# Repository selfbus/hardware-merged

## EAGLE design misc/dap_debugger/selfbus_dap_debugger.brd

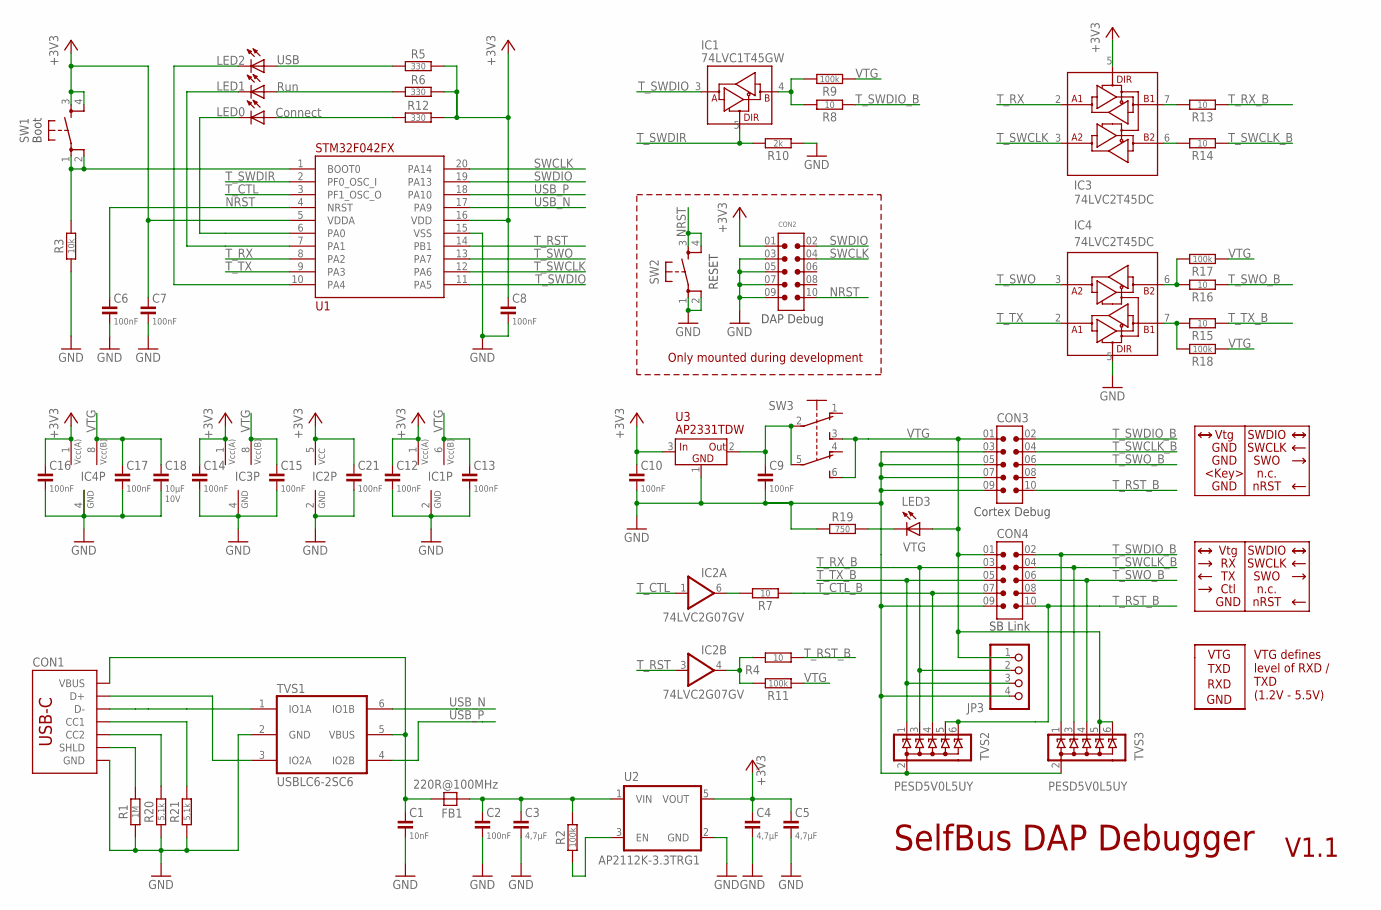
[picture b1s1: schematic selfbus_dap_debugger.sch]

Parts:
C1: 10nF; C0805
C2, C6, C7, C8, C9, C10, C12, C13, C14, C15, C16, C17, C21: 100nF; C0805
C3, C4, C5: 4,7µF; C0805
C18: 10µF; C0805; VOLTAGE 10V
CON1: XKB U262-161N-4BVC11; USB-C-16P-2LAYER-PADS
CON2, CON3: SHF-105-01-X-D-TH; SAMTEC_SHF-105-01-X-D-TH
CON4: SAMTEC-LTMM-105-02-T-D
FB1: 220R@100MHz; FB0805; MOUSER# 810-MPZ2012S221ATD25; LCSC#2 C139188
IC1: 74LVC1T45GW; SOT363; MOUSER# 771-74LVC1T45GW125; LCSC# C478004
IC2: 74LVC2G07GV; SOT23-6; MOUSER# 771-LVC2G07GV125; LCSC# C548568
IC3: 74LVC2T45DC; VSSOP8(0.5); MOUSER# 595-SN74LVC2T45DCUT; LCSC# C15741
IC4: 74LVC2T45DC; VSSOP8(0.5)
JP3: PINHD-1X4; 1X04
LED0: Connect; LED_3MM_GREEN
LED1: Run; LED_3MM_YELLOW
LED2: USB; LED_3MM_GREEN
LED3: VTG; LED_3MM_RED
R1: 1M; R0805
R2, R9, R11, R17, R18: 100k; R0805
R3: 10k; R0805
R4, R7, R8, R13, R14, R15, R16: 10; R0805
R5, R6, R12: 330; R0805
R10: 2k; R0805
R19: 750; R0805
R20, R21: 5,1k; R0805
SW1: BOOT; TACT_SWITCH_6X6_SNAP-IN_17; MOUSER# 688-SKHHDHA010; LCSC# C139811
SW2: RESET; TACT_SWITCH_6X6_SNAP-IN_17; MOUSER# 688-SKHHDHA010; LCSC# C139811
SW3: XKB7070-Z; XKB7070
TVS1: USBLC6-2SC6; SOT-23-6L; MOUSER# 511-USBLC6-2SC6; LCSC#2 C2687116
TVS2: PESD5V0L5UY; SOT363; MOUSER# 771-PESD5V0L5UY-T/R; LCSC# C179747
TVS3: PESD5V0L5UY; SOT363
U1: STM32F042FX; TSSOP20; MOUSER# 511-STM32F042F4P6; LCSC# C81002
U2: AP2112K-3.3TRG1; SOT23-5; MOUSER# 621-AP2112K-3.3TRG1; LCSC# C51118
U3: AP2331TDW; SC59; MOUSER# 621-AP2331W-7; LCSC# C460346

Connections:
+3V3: C4.1, C5.1, C7.1, C8.1, C10.1, C12.1, C14.1, C16.1, C21.1, CON2.01 (1), IC1.1 (VCC(A)), IC2.5 (VCC), IC3.1 (VCC(A)), IC3.5 (DIR), IC4.1 (VCC(A)), R5.2, R6.2, R12.2, SW1.3, SW1.4, U1.5 (VDDA), U1.16 (VDD), U2.5 (VOUT), U3.3 (IN)
D_N: CON1.A7 (D-), CON1.B7 (D-), TVS1.1 (IO1A)
D_P: CON1.A6 (D+), CON1.B6 (D+), TVS1.3 (IO2A)
GND: C1.2, C2.2, C3.2, C4.2, C5.2, C6.2, C7.2, C8.2, C9.2, C10.2, C12.2, C13.2, C14.2, C15.2, C16.2, C17.2, C18.2, C21.2, CON1.GND, CON1.GND2 (GND), CON2.03 (3), CON2.05 (5), CON2.07 (7), CON2.09 (9), CON3.03 (3), CON3.05 (5), CON3.07 (7), CON3.09 (9), CON4.09 (9), IC1.2 (GND), IC2.2 (GND), IC3.4 (GND), IC4.4 (GND), IC4.5 (DIR), JP3.4, R1.1, R3.1, R10.1, R19.1, R20.1, R21.1, SW2.1, SW2.2, TVS1.2 (GND), TVS2.2 (A), TVS3.2 (A), U1.15 (VSS), U2.2 (GND), U3.1 (GND)
LED0: LED0.C, U1.6 (PA0)
LED1: LED1.C, U1.7 (PA1)
unnamed: CON1.SHLD1 (SHLD), CON1.SHLD2 (SHLD), CON1.SHLD3 (SHLD), CON1.SHLD4 (SHLD), R1.2
unnamed: CON1.B5 (CC2), R20.2
unnamed: CON1.A5 (CC1), R21.2
unnamed: R2.1, U2.3 (EN)
unnamed: C2.1, C3.1, FB1.2, R2.2, U2.1 (VIN)
unnamed: IC2.4 (OUT), R4.2, R11.2
unnamed: IC2.6 (OUT), R7.2
unnamed: R3.2, SW1.1, SW1.2, U1.1 (BOOT0)
unnamed: LED2.A, R5.1
unnamed: LED1.A, R6.1
unnamed: C9.1, SW3.2, SW3.5, U3.2 (OUT)
unnamed: LED0.A, R12.1
unnamed: IC3.7 (B1), R13.2
unnamed: IC3.6 (B2), R14.2
unnamed: IC4.6 (B2), R16.2, R17.2
unnamed: IC4.7 (B1), R15.2, R18.2
unnamed: IC1.4 (B), R8.2, R9.2
unnamed: LED2.C, U1.10 (PA4)
unnamed: LED3.C, R19.2
NRST: C6.1, CON2.10, SW2.3, SW2.4, U1.4 (NRST)
SWCLK: CON2.04 (4), U1.20 (PA14)
SWDIO: CON2.02 (2), U1.19 (PA13)
T_CTL: IC2.1 (IN), U1.3 (PF1_OSC_O)
T_CTL_B: CON4.07 (7), R7.1, TVS2.4 (C3)
T_RST: IC2.3 (IN), U1.14 (PB1)
T_RST_B: CON3.10, CON4.10, R4.1, TVS2.5 (C4), TVS2.6 (C5)
T_RX: IC3.2 (A1), U1.8 (PA2)
T_RX_B: CON4.03 (3), JP3.2, R13.1, TVS2.3 (C2)
T_SWCLK: IC3.3 (A2), U1.12 (PA6)
T_SWCLK_B: CON3.04 (4), CON4.04 (4), R14.1, TVS3.3 (C2)
T_SWDIO: IC1.3 (A), U1.11 (PA5)
T_SWDIO_B: CON3.02 (2), CON4.02 (2), R8.1, TVS3.1 (C1)
T_SWDIR: IC1.5 (DIR), R10.2, U1.2 (PF0_OSC_I)
T_SWO: IC4.3 (A2), U1.13 (PA7)
T_SWO_B: CON3.06 (6), CON4.06 (6), R16.1, TVS3.4 (C3)
T_TX: IC4.2 (A1), U1.9 (PA3)
T_TX_B: CON4.05 (5), JP3.3, R15.1, TVS2.1 (C1)
USB_N: TVS1.6 (IO1B), U1.17 (PA9)
USB_P: TVS1.4 (IO2B), U1.18 (PA10)
VBUS: C1.1, CON1.VBUS1 (VBUS), CON1.VBUS2 (VBUS), FB1.1, TVS1.5 (VBUS)
VTG: C13.1, C15.1, C17.1, C18.1, CON3.01 (1), CON4.01 (1), IC1.6 (VCC(B)), IC3.8 (VCC(B)), IC4.8 (VCC(B)), JP3.1, LED3.A, R9.1, R11.1, R17.1, R18.1, SW3.3 (S), SW3.6 (S), TVS3.5 (C4), TVS3.6 (C5)

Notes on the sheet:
SelfBus DAP Debugger
V1.1
DAP Debug
Only mounted during development
SB Link
Cortex Debug
Vtg
GND
Ctl
SWDIO
SWCLK
SWO
nRST
<Key>
n.c.
TXD
RXD
VTG
VTG defines level of RXD / TXD (1.2V - 5.5V)
Boot
RESET

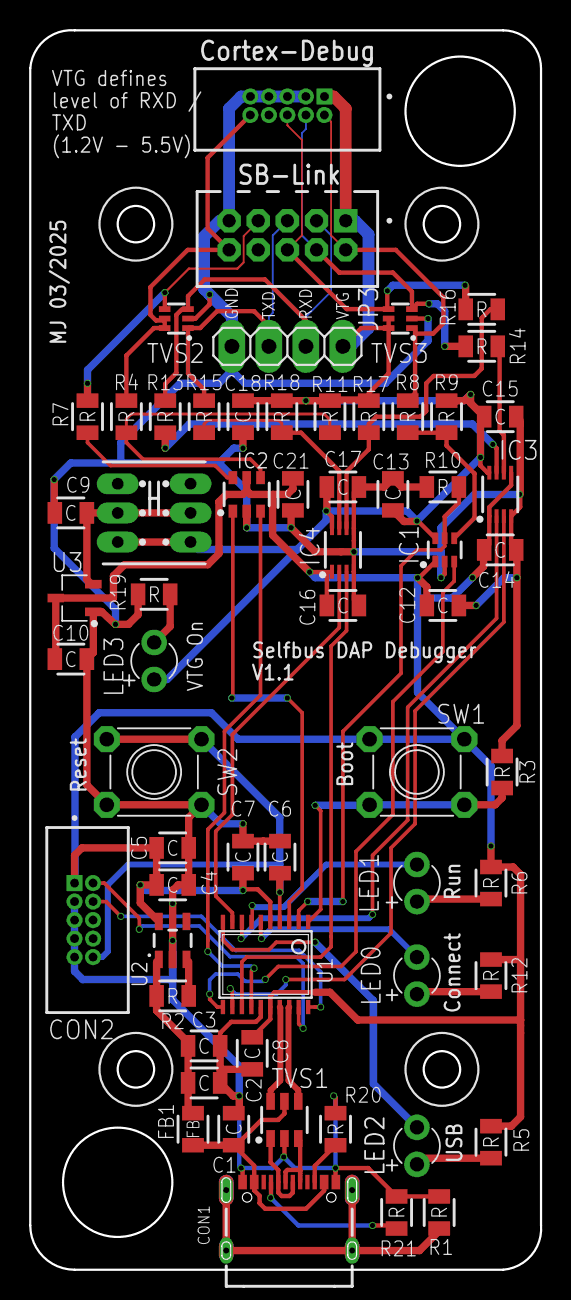
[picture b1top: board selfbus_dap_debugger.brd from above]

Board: 2 copper layers, 35.1 x 85.1 mm, 62 parts (0 on the bottom side), 47 nets.

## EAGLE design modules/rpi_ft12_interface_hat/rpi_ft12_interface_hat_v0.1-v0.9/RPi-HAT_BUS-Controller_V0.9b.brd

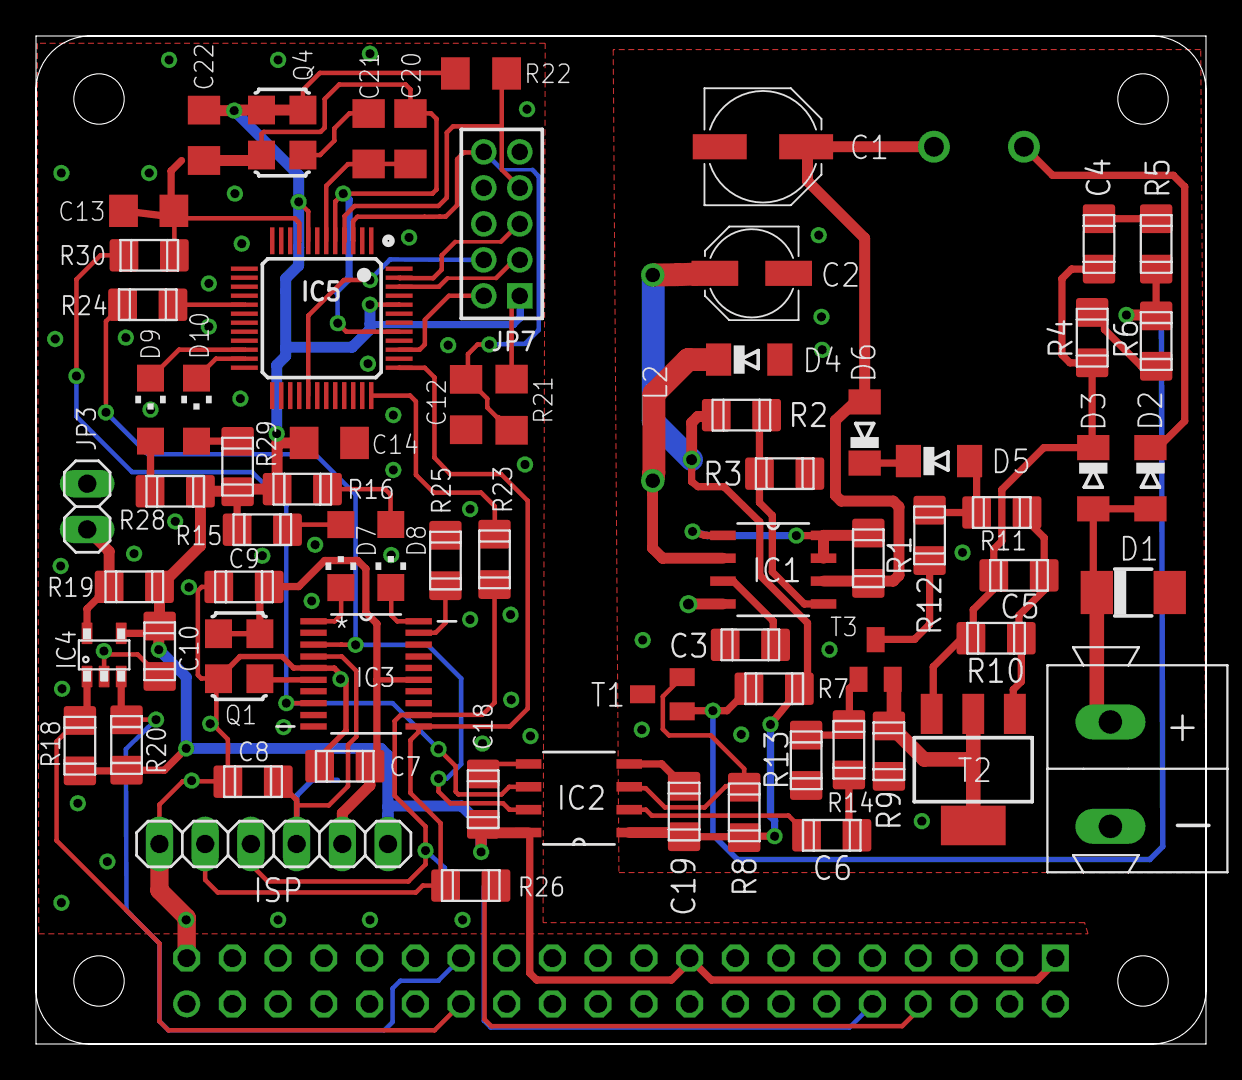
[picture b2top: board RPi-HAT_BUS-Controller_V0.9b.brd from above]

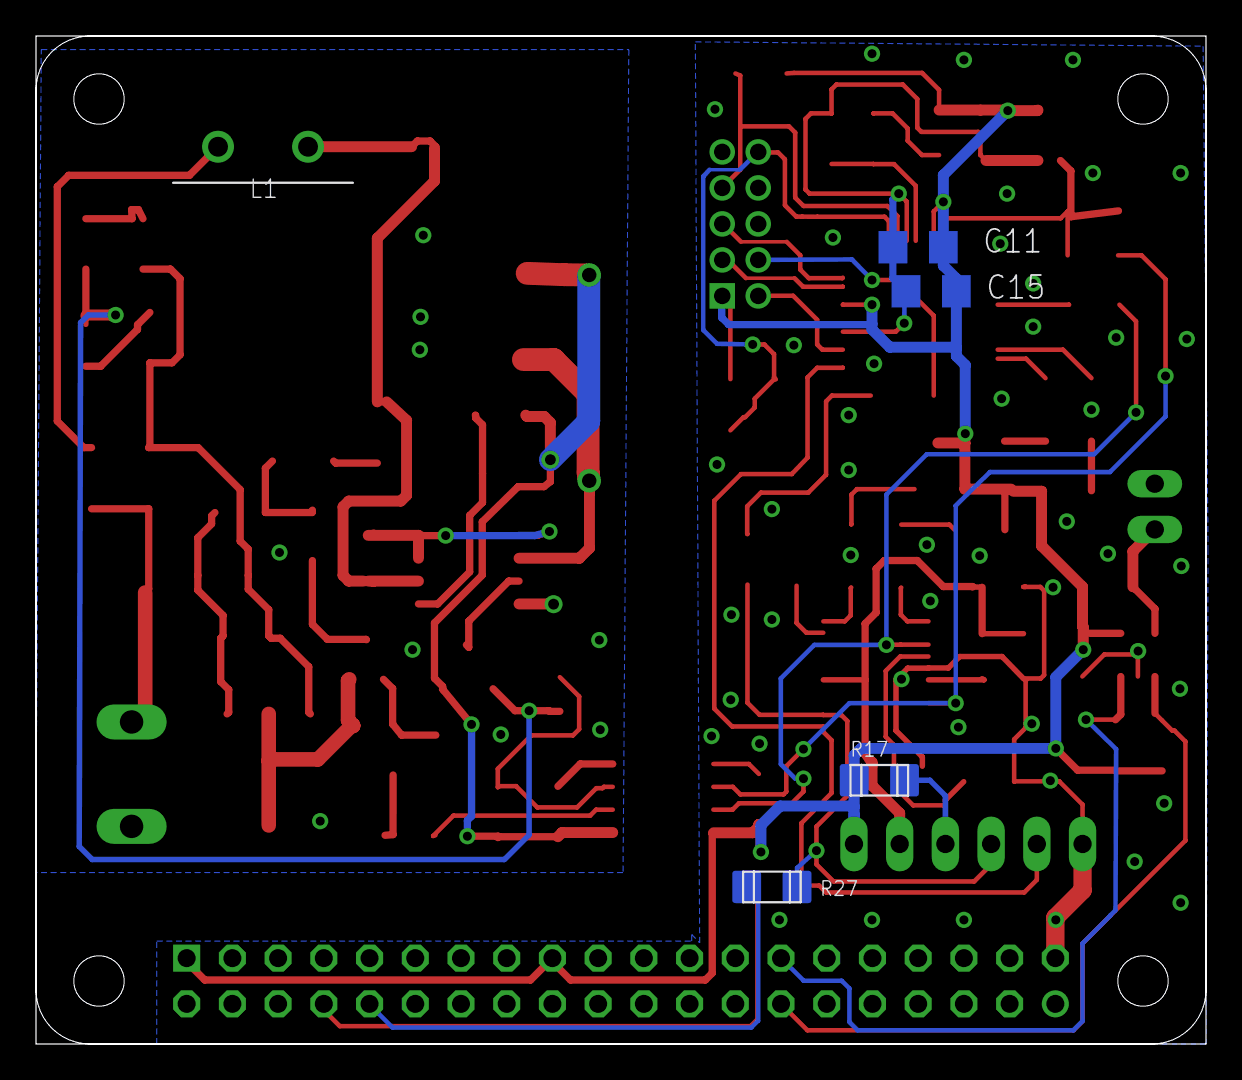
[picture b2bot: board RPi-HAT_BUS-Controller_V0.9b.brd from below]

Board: 2 copper layers, 65.0 x 56.0 mm, 77 parts (5 on the bottom side), 55 nets.

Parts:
C1: 100µF; PANASONIC_D
C2: 100µF; PANASONIC_C
C3: 470p; R1206
C4, C7, C8: 100n; R1206
C5, C6, C9: 10n; R1206
C10, C18, C19: 100nF; R1206
C11, C12, C22: 10n; C1206
C13, C21: 100p; C1206
C14, C15: 100n; C1206
C20: 220p; C1206
D1: SMAJ40AC; DO-214AC
D2, D3, D6: 1N4148; MINIMELF
D4: BAT46; MINIMELF
D5: 7V5; MINIMELF
D7: green; CHIPLED_1206
D8, D9, D10: red; CHIPLED_1206
IC1: MC34063AD; SOIC127P600X175-8N
IC2: ADUM1201ARZ; SOIC127P600X175-8N
IC3: P89LPC922FDH,512FDH; SOP65P640X110-20N
IC4: 24LC-I/OT; SOT23-5
IC5: LPC1115; LQFP48
ISP: PINHD-1X6-ISP; 1X06
JP2: RPI_B+; RPI-B+HAT
JP3: 1X02
JP7: J; 2X05M
L1: 150mH; 11P-L1
L2: 220µH; 2200-11.43
Q1: ASF1; ASF
Q4: ASFL; ASF
R1: 3R3; R1206
R2: 3k6; R1206
R3, R10, R12: 2k2; R1206
R4, R13, R21, R22: 100k; R1206
R5, R8: 10k; R1206
R6: 47k; R1206
R7: 82k; R1206
R9: 5R6; R1206
R11, R15, R16, R19, R25, R28, R29: 1k; R1206
R14: 5k6; R1206
R17: 4k7; R1206
R18, R20: 3k9; R1206
R23, R24, R26, R27: 330; R1206
R30: 100; R1206
T1: BC856; SOT23
T2: BCP52; SOT223
T3: BC847; SOT23
U$1: WAGO-243-211

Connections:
+3V3: C2.+, C19.2, IC2.1, L2.1, R2.2, R7.2, R8.2
+3V3/2: C10.2, C11.2, C14.2, C15.2, C18.2, C22.2, IC2.8, IC4.4, IC5.8, IC5.44, ISP.1, JP2.1, JP2.17, JP7.1, Q4.1, Q4.4, R15.2, R16.2, R17.2, R18.2, R19.2, R20.2, R21.2, R22.2, R28.1, R29.1
EIBOUT_ARM: IC5.17, R24.2
EIB_IN: IC2.6, IC3.8, R30.1
EIB_OUT: IC2.7, IC3.3, R24.1
GND: C1.-, C2.-, C3.1, C19.1, D1.A, D4.A, IC1.4, IC2.4, R3.1, R4.1, R6.1, R9.1, R13.1, T1.3, U$1.2-
GND/2: C7.1, C8.1, C9.1, C10.1, C11.1, C12.1, C13.1, C14.1, C15.1, C18.1, C20.1, C22.1, IC2.5, IC3.5, IC4.2, IC5.5, IC5.41, ISP.6, JP2.6, JP2.9, JP2.14, JP2.20, JP2.25, JP2.30, JP2.34, JP2.39, JP3.2, JP7.9, Q1.2, Q4.2, R25.1
ID_SC: IC4.1, JP2.28, R18.1
ID_SD: IC4.3, JP2.27, R20.1
ISP_EN: IC5.4, JP7.7, R22.1
ISP_RXD: IC5.46, JP7.3
ISP_TXD: IC5.47, JP7.5
KNX-IN: IC2.3, R8.1, T1.2
KNX-OUT: C6.2, IC2.2
LPC_VCC: C7.2, C9.2, IC3.15, ISP.2, Q1.1, Q1.4
unnamed: D1.C, D2.A, D3.A, U$1.1+
unnamed: C13.2, IC5.9, R30.2
unnamed: IC1.5, R2.1, R3.2
unnamed: C4.2, R5.1
unnamed: D2.C, L1.2
unnamed: R5.2, R6.2, R7.1, T1.1
unnamed: IC1.1, IC1.7, IC1.8, R1.2
unnamed: D8.C, IC3.20
unnamed: C3.2, IC1.3
unnamed: D7.C, IC3.1
unnamed: IC4.5, JP3.1, R19.1
unnamed: D4.C, IC1.2, L2.2
unnamed: IC3.19, R25.2
unnamed: D10.A, R29.2
unnamed: D9.A, R28.2
unnamed: JP2.8, R26.1
unnamed: JP2.10, R27.1
unnamed: D10.C, IC5.23
unnamed: D9.C, IC5.22
unnamed: C20.2, C21.2, IC5.6
unnamed: C21.1, Q4.3
unnamed: R9.2, T2.2, T2.4, T3.2
unnamed: C5.2, R10.2, R11.1, T2.1
unnamed: D5.A, R11.2, R12.2
unnamed: R12.1, T3.3
unnamed: R13.2, R14.1, T3.1
unnamed: C6.1, R14.2
unnamed: D5.C, D6.C
unnamed: IC3.6, Q1.3
unnamed: D7.A, R15.1
unnamed: D8.A, R16.1
RESET: C12.2, IC5.3, JP7.10, R21.1
RST: C8.2, IC3.4, ISP.3, R17.1
RXD: IC3.11, IC5.37, ISP.5, R26.2
SWCLK: IC5.29, JP7.4
SWDIO: IC5.39, JP7.2
TXD: IC3.12, ISP.4, R23.2, R27.2
TXD_ARM: IC5.36, R23.1
V+: C4.1, C5.1, D3.C, R4.2, R10.1, T2.3
VDD: C1.+, D6.A, IC1.6, L1.1, R1.1

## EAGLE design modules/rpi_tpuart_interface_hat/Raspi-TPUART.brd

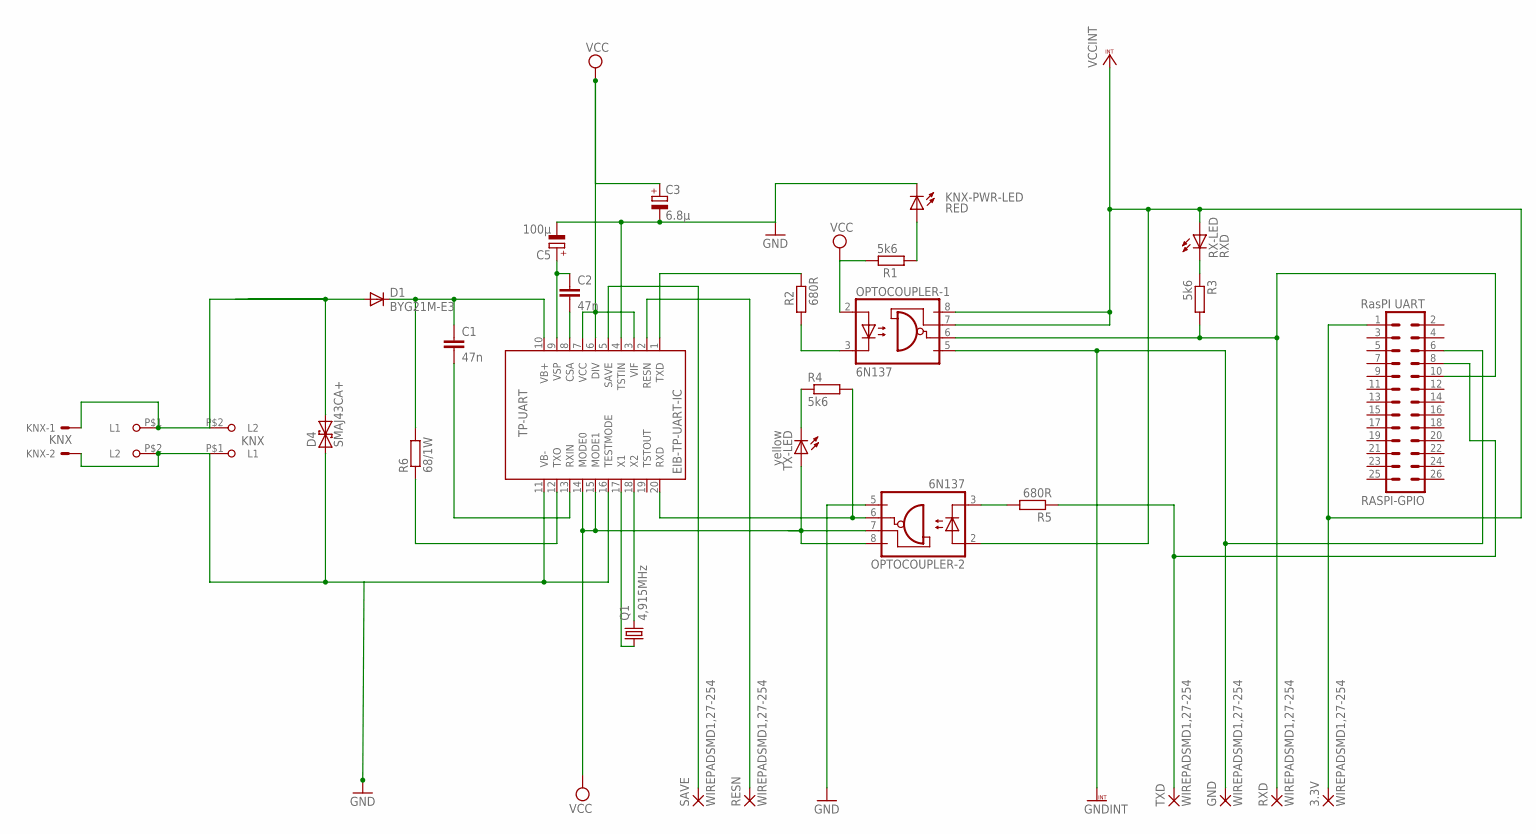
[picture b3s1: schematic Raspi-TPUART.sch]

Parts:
3.3V: WIREPADSMD1,27-254; SMD1,27-2,54
C1, C2: 47n; C1206
C3: 6.8µ; D/7343-31R
C5: 100µ; D/7343-31R
D1: BYG21M-E3; SMB
D4: SMAJ43CA+; DO214AA
EIB-TP-UART-IC: TP-UART; SOIC20
GND: WIREPADSMD1,27-254; SMD1,27-2,54
KNX: KNX; 22-23-2021
KNX-PWR-LED: RED; KA-3528ASYC
KNX_WAGO_243: 243-211
OPTOCOUPLER-1, OPTOCOUPLER-2: 6N137; DIL8-SMD
Q1: 4,915MHz; HC49UP
R1, R3, R4: 5k6; M1206
R2, R5: 680R; M1206
R6: 68/1W; R2512
RASPI-GPIO: RasPI UART; MA13-2
RESN: WIREPADSMD1,27-254; SMD1,27-2,54
RX-LED: RXD; KA-3528ASYC
RXD: WIREPADSMD1,27-254; SMD1,27-2,54
SAVE: WIREPADSMD1,27-254; SMD1,27-2,54
TX-LED: yellow; KA-3528ASYC
TXD: WIREPADSMD1,27-254; SMD1,27-2,54
U$1: 243-211

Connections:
CSA: C2.2, EIB-TP-UART-IC.8 (CSA)
GND: C3.-, C5.-, D4.A (1), EIB-TP-UART-IC.4 (TSTIN), EIB-TP-UART-IC.11 (VB-), EIB-TP-UART-IC.16 (TESTMODE), KNX.2, KNX-PWR-LED.C, KNX_WAGO_243.P$1 (L1), OPTOCOUPLER-2.5 (GND), U$1.P$2 (L2)
GNDINT: GND.1, OPTOCOUPLER-1.5 (GND), RASPI-GPIO.6
KNX+: D1.A, D4.C (2), KNX.1, KNX_WAGO_243.P$2 (L2), U$1.P$1 (L1)
unnamed: R3.1, RX-LED.C
unnamed: R4.1, TX-LED.C
unnamed: OPTOCOUPLER-2.3 (C), R5.2
unnamed: KNX-PWR-LED.A, R1.1
RASPI_RXD: OPTOCOUPLER-1.6 (VO), R3.2, RASPI-GPIO.10, RXD.1
RASPI_TXD: R5.1, RASPI-GPIO.8, TXD.1
RESN: EIB-TP-UART-IC.2 (RESN), RESN.1
RXD: EIB-TP-UART-IC.20 (RXD), OPTOCOUPLER-2.6 (VO), R4.2
RXIN: C1.2, EIB-TP-UART-IC.13 (RXIN)
SAVE: EIB-TP-UART-IC.5 (SAVE), SAVE.1
TXD: EIB-TP-UART-IC.1 (TXD), R2.2
TXD1: OPTOCOUPLER-1.3 (C), R2.1
TXO: EIB-TP-UART-IC.12 (TXO), R6.1
VB+: C1.1, D1.C, EIB-TP-UART-IC.10 (VB+), R6.2
VCC: C3.+, EIB-TP-UART-IC.3 (VIF), EIB-TP-UART-IC.6 (DIV), EIB-TP-UART-IC.7 (VCC), EIB-TP-UART-IC.14 (MODE0), EIB-TP-UART-IC.15 (MODE1), OPTOCOUPLER-1.2 (A), OPTOCOUPLER-2.7 (VE), OPTOCOUPLER-2.8 (VCC), R1.2, TX-LED.A
VCCINT: 3.3V.1, OPTOCOUPLER-1.7 (VE), OPTOCOUPLER-1.8 (VCC), OPTOCOUPLER-2.2 (A), RASPI-GPIO.1, RX-LED.A
VSP: C2.1, C5.+, EIB-TP-UART-IC.9 (VSP)
X1: EIB-TP-UART-IC.17 (X1), Q1.1
X2: EIB-TP-UART-IC.18 (X2), Q1.2

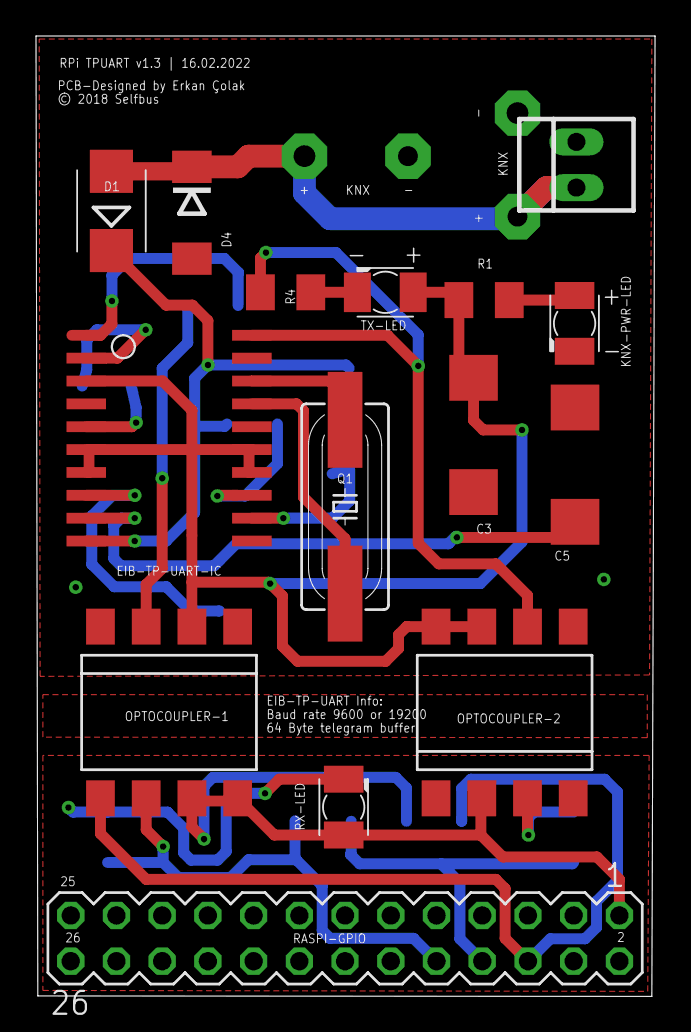
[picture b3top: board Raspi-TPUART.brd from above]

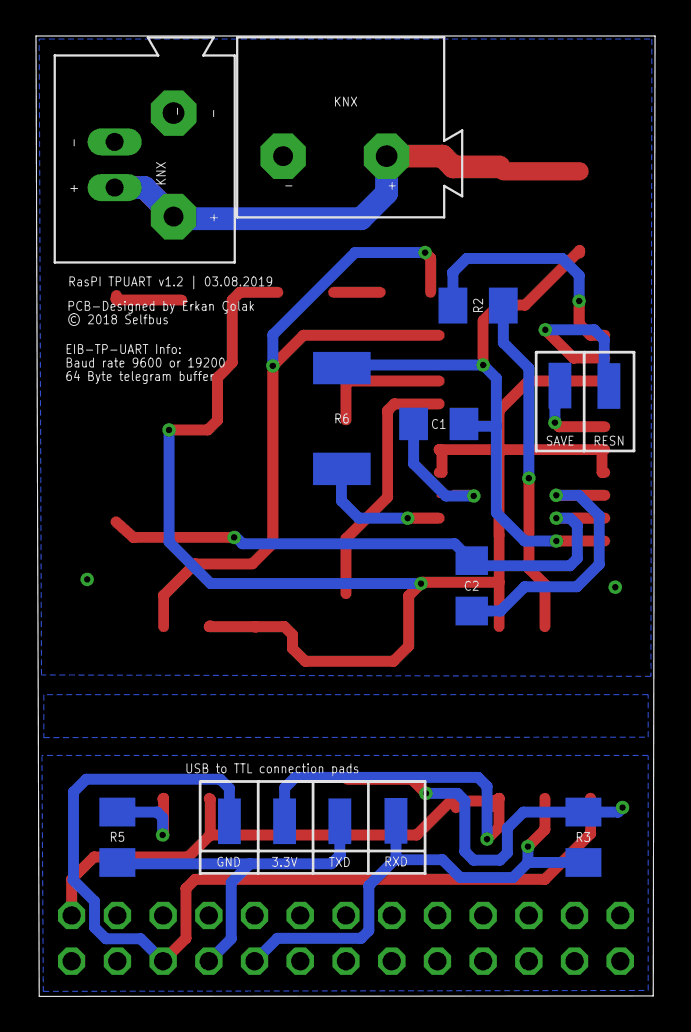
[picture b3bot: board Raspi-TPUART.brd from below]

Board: 2 copper layers, 34.4 x 53.4 mm, 29 parts (14 on the bottom side), 23 nets.

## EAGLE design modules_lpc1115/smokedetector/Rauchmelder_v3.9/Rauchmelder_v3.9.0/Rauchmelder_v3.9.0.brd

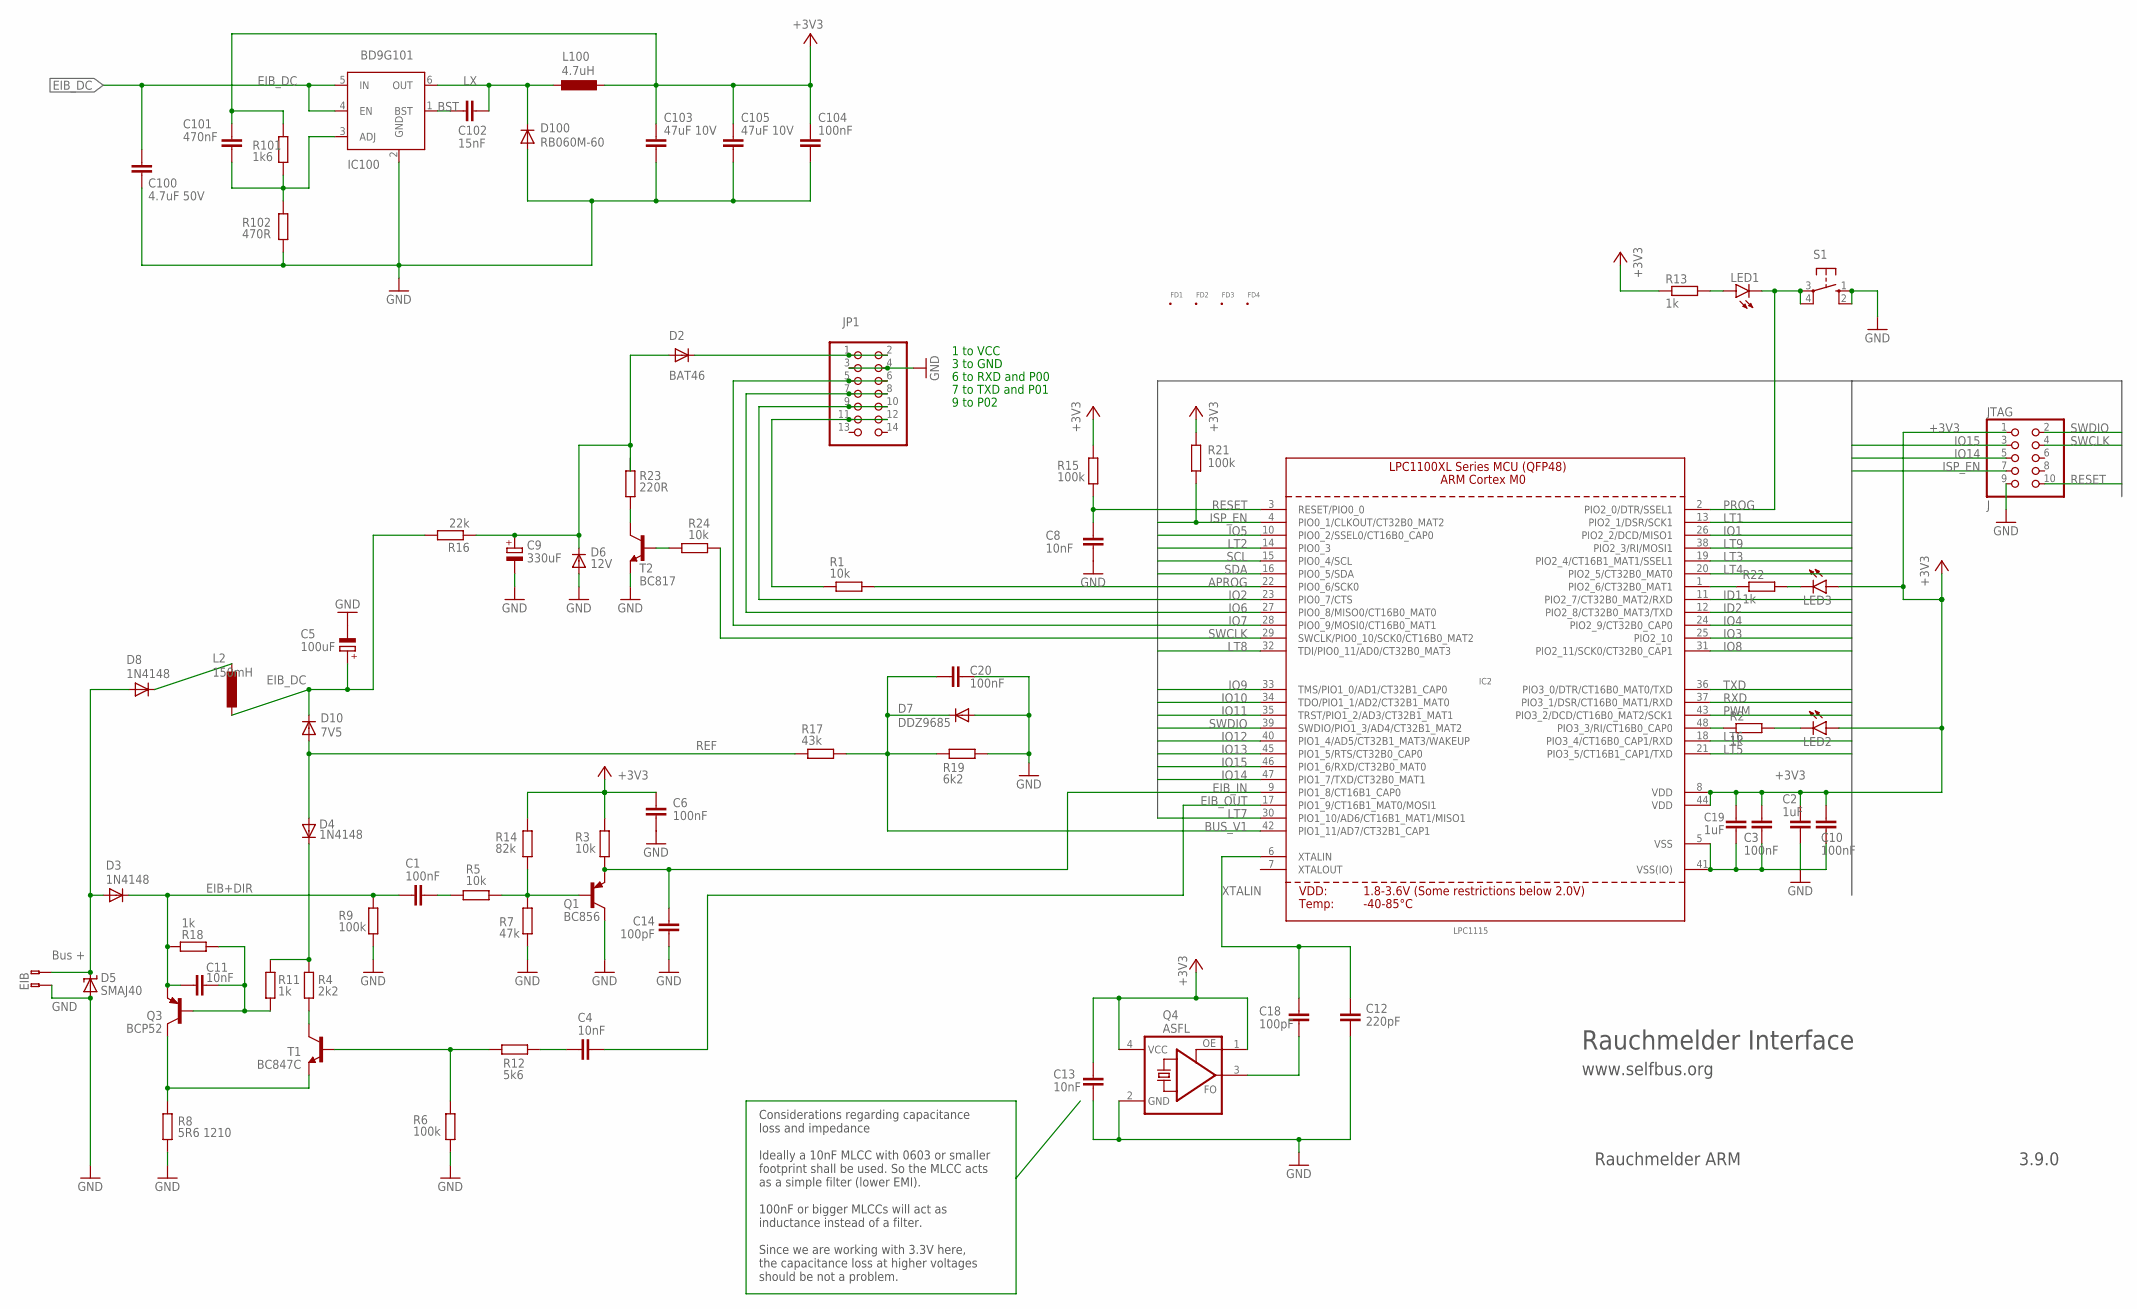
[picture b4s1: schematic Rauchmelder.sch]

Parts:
C1, C3, C6, C10, C20, C104: 100nF; C0805
C2, C19: 1uF; C0805
C4, C8, C11, C13: 10nF; C0805
C5: 100uF; SANYO-OSCON_SMD_C6
C9: 330uF; E3,5-8
C12: 220pF; C0805
C14, C18: 100pF; C0805
C100: 4.7uF 50V; C0805
C101: 470nF; C0805
C102: 15nF; C0805
C103, C105: 47uF 10V; C0805
D2: BAT46; SOD-123
D3, D4, D8: 1N4148; SOD-123
D5: SMAJ40; SMBJ
D6: 12V; SOD-123
D7: DDZ9685; SOD-123
D10: 7V5; SOD-123
D100: RB060M-60; SOD-123
FD1, FD2, FD3, FD4: FID_40MIL; FID_040
IC2: LPC1115; LQFP48
IC100: BD9G101; SOT23-6
JP1: PINHD-2X7; 2X07
JTAG: J; 2X05M
L2: 150mH; 11P-L1
L100: 4.7uH; L4532P
LED1, LED2, LED3: LEDCHIPLED_0805; CHIPLED_0805
Q1: BC856; SOT23-BEC
Q3: BCP52; SOT223
Q4: ASFL; ASF
R1, R3, R5, R24: 10k; R0805
R2, R11, R13, R18, R22: 1k; R0805
R4: 2k2; R0805
R6, R9, R15, R21: 100k; R0805
R7: 47k; R0805
R8: 5R6 1210; R1210
R12: 5k6; R0805
R14: 82k; R0805
R16: 22k; R0805
R17: 43k; R0805
R19: 6k2; R0805
R23: 220R; R2512
R101: 1k6; R0805
R102: 470R; R0805
S1: 10-XX; B3F-10XX
T1: BC847C; SOT23
T2: BC817; SOT23-WIDE
U$1: EIB; BUSKLEMME243-724

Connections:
+3V3: C2.2, C3.2, C6.2, C10.2, C13.2, C19.2, C101.2, C103.1, C104.1, C105.1, IC2.8 (VDD), IC2.44 (VDD), JTAG.1, L100.2, LED2.A, LED3.A, Q4.1 (OE), Q4.4 (VCC), R3.2, R13.1, R14.2, R15.1, R21.2, R101.2
APROG: IC2.22 (PIO0_6/SCK0)
ARMINFO1: IC2.48 (PIO3_3/RI/CT16B0_CAP0), R2.1
ARMINFO2: IC2.1 (PIO2_6/CT32B0_MAT1), R22.1
BST: C102.2, IC100.1 (BST)
BUS_V1: C20.2, D7.C, IC2.42 (PIO1_11/AD7/CT32B1_CAP1), R17.2, R19.1
EIB+: D3.A, D5.C, D8.A, U$1.2 (B-2)
EIB+DIR: C1.1, C11.1, D3.C, Q3.3 (E), R9.2, R18.2
EIB_DC: C5.+, C100.2, D10.C, IC100.4 (EN), IC100.5 (IN), L2.2, R16.2
EIB_IN: C14.2, IC2.9 (PIO1_8/CT16B1_CAP0), Q1.E, R3.1
EIB_OUT: C4.2, IC2.17 (PIO1_9/CT16B1_MAT0/MOSI1)
FB1: C101.1, IC100.3 (ADJ), R101.1, R102.2
GND: C2.1, C3.1, C5.-, C6.1, C8.1, C9.-, C10.1, C12.1, C13.1, C14.1, C19.1, C20.1, C100.1, C103.2, C104.2, C105.2, D5.A, D6.A, D7.A, D100.A, IC2.5 (VSS), IC2.41 (VSS(IO)), IC100.2 (GND), JP1.3, JP1.4, JTAG.9, Q1.C, Q4.2 (GND), R6.1, R7.1, R8.1, R9.1, R19.2, R102.1, S1.1 (S), S1.2 (S1), T2.2 (E), U$1.1 (B-1)
ID1: IC2.11 (PIO2_7/CT32B0_MAT2/RXD)
ID2: IC2.12 (PIO2_8/CT32B0_MAT3/TXD)
IO1: IC2.26 (PIO2_2/DCD/MISO1)
IO2: IC2.23 (PIO0_7/CTS)
IO3: IC2.25 (PIO2_10)
IO4: IC2.24 (PIO2_9/CT32B0_CAP0)
IO5: IC2.10 (PIO0_2/SSEL0/CT16B0_CAP0)
IO6: IC2.27 (PIO0_8/MISO0/CT16B0_MAT0)
IO7: IC2.28 (PIO0_9/MOSI0/CT16B0_MAT1)
IO8: IC2.31 (PIO2_11/SCK0/CT32B0_CAP1)
IO9: IC2.33 (TMS/PIO1_0/AD1/CT32B1_CAP0)
IO10: IC2.34 (TDO/PIO1_1/AD2/CT32B1_MAT0)
IO11: IC2.35 (TRST/PIO1_2/AD3/CT32B1_MAT1)
IO12: IC2.40 (PIO1_4/AD5/CT32B1_MAT3/WAKEUP)
IO13: IC2.45 (PIO1_5/RTS/CT32B0_CAP0)
IO14: IC2.47 (PIO1_7/TXD/CT32B0_MAT1), JTAG.5
IO15: IC2.46 (PIO1_6/RXD/CT32B0_MAT0), JTAG.3
ISP_EN: IC2.4 (PIO0_1/CLKOUT/CT32B0_MAT2), JTAG.7, R21.1
LT1: IC2.13 (PIO2_1/DSR/SCK1), R24.2
LT2: IC2.14 (PIO0_3)
LT3: IC2.19 (PIO2_4/CT16B1_MAT1/SSEL1)
LT4: IC2.20 (PIO2_5/CT32B0_MAT0)
LT5: IC2.21 (PIO3_5/CT16B1_CAP1/TXD), JP1.9, JP1.10
LT6: IC2.18 (PIO3_4/CT16B0_CAP1/RXD)
LT7: IC2.30 (PIO1_10/AD6/CT16B1_MAT1/MISO1)
LT8: IC2.32 (TDI/PIO0_11/AD0/CT32B0_MAT3), R1.2
LT9: IC2.38 (PIO2_3/RI/MOSI1)
LX: C102.1, D100.C, IC100.6 (OUT), L100.1
unnamed: JP1.11, JP1.12, R1.1
unnamed: Q1.B, R5.2, R7.2, R14.1
unnamed: LED3.C, R22.2
unnamed: C11.2, Q3.1 (B), R11.1, R18.1
unnamed: LED2.C, R2.2
unnamed: R23.2, T2.3 (C)
unnamed: R24.1, T2.1 (B)
unnamed: LED1.A, R13.2
unnamed: C9.+, D2.A, D6.C, R16.1, R23.1
unnamed: D8.C, L2.1
unnamed: C1.2, R5.1
unnamed: D2.C, JP1.1, JP1.2
unnamed: C4.1, R12.1
unnamed: R4.1, T1.3 (C)
unnamed: D4.C, R4.2, R11.2
unnamed: Q3.2 (C), Q3.4 (C), R8.2, T1.2 (E)
unnamed: R6.2, R12.2, T1.1 (B)
unnamed: C18.1, Q4.3 (FO)
PROG: IC2.2 (PIO2_0/DTR/SSEL1), LED1.C, S1.3, S1.4 (P1)
PWM: IC2.43 (PIO3_2/DCD/CT16B0_MAT2/SCK1)
REF: D4.A, D10.A, R17.1
RESET: C8.2, IC2.3 (RESET/PIO0_0), JTAG.10, R15.2
RXD: IC2.37 (PIO3_1/DSR/CT16B0_MAT1/RXD), JP1.5, JP1.6
SCL: IC2.15 (PIO0_4/SCL)
SDA: IC2.16 (PIO0_5/SDA)
SWCLK: IC2.29 (SWCLK/PIO0_10/SCK0/CT16B0_MAT2), JTAG.4
SWDIO: IC2.39 (SWDIO/PIO1_3/AD4/CT32B1_MAT2), JTAG.2
TXD: IC2.36 (PIO3_0/DTR/CT16B0_MAT0/TXD), JP1.7, JP1.8
XTALIN: C12.2, C18.2, IC2.6 (XTALIN)

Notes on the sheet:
Bus +
GND
Rauchmelder Interface
www.selfbus.org
Rauchmelder ARM
3.9.0
6 to RXD and P00
7 to TXD and P01
9 to P02
1 to VCC
3 to GND
Considerations regarding capacitance loss and impedance Ideally a 10nF MLCC with 0603 or smaller footprint shall be used. So the MLCC acts as a simple filter (lower EMI). 100nF or bigger MLCCs will act as inductance instead of a filter. Since we are working with 3.3V here, the capacitance loss at h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

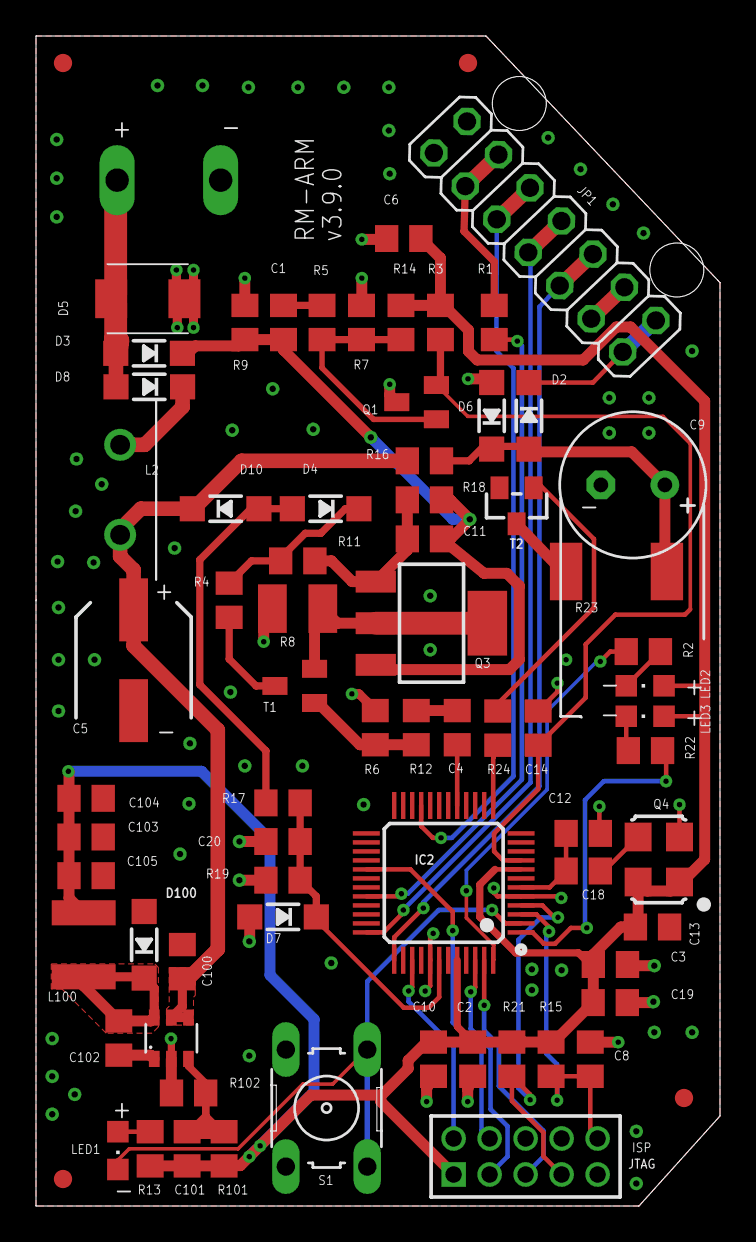
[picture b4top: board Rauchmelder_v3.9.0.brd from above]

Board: 2 copper layers, 38.0 x 65.0 mm, 75 parts (0 on the bottom side), 45 nets.

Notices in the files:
modules/rpi_tpuart_interface_hat/Raspi-TPUART.brd:
© 2018 Selfbus
parts and their libraries:
microbuilder: This work is placed in the public domain, and may be freely used for commercial and non-commercial work with the following conditions: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
Eagle_WR-WTB: Copyright: Würth Elektronik
